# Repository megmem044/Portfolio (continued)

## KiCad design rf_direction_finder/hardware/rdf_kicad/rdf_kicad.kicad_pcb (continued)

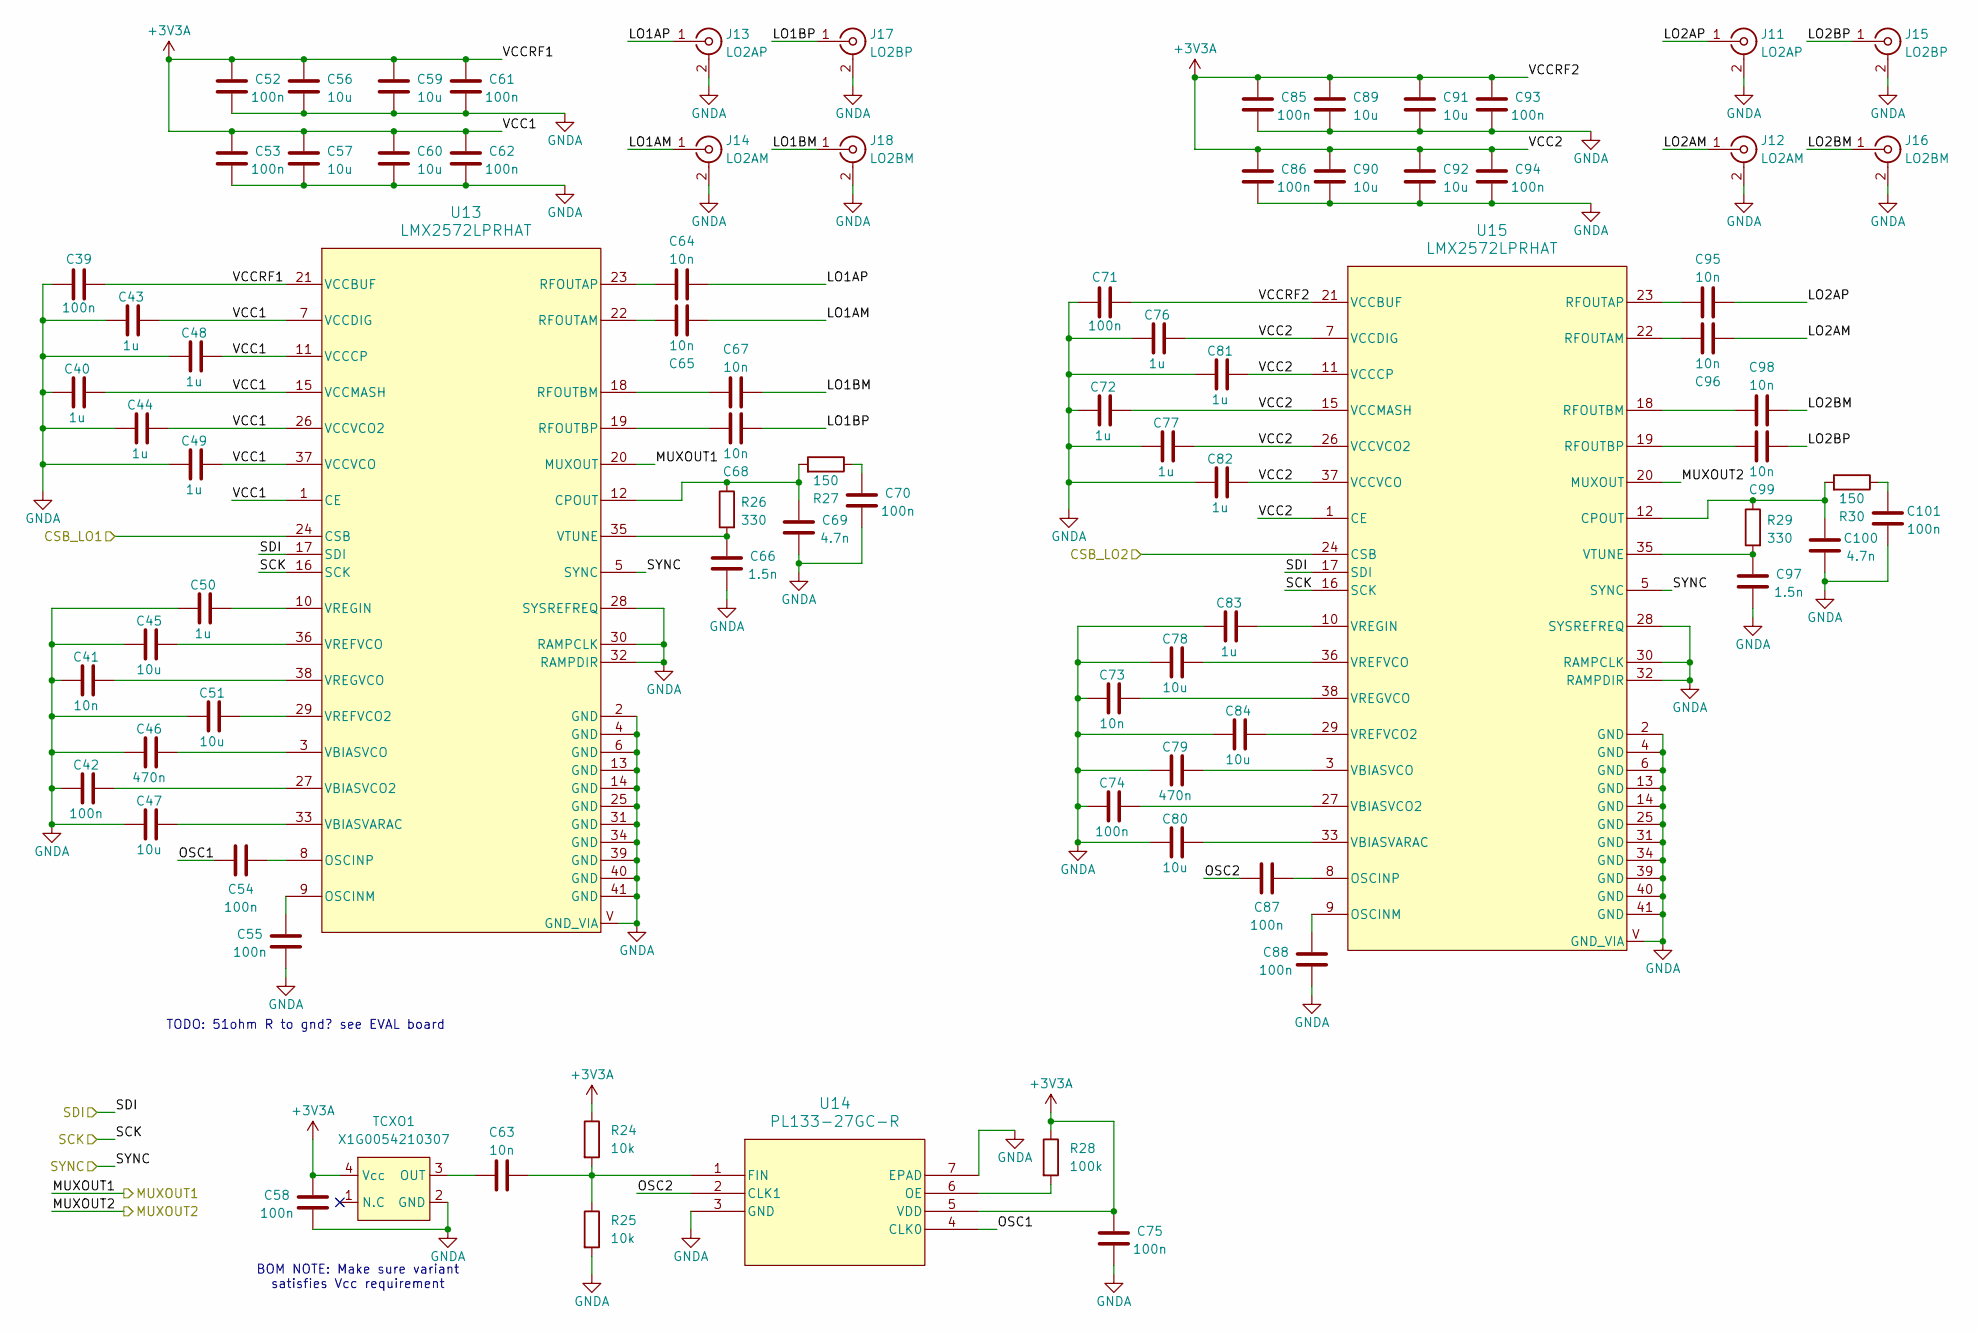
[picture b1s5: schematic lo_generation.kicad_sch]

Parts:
C39, C42, C52, C53, C55, C58, C61, C62, C70, C71, C74, C75, C85, C86, C88, C93, C94, C101: 100n; C_0603_1608Metric_Pad1.08x0.95mm_HandSolder
C40, C43, C44, C48, C49, C50, C72, C76, C77, C81, C82, C83: 1u; C_0603_1608Metric_Pad1.08x0.95mm_HandSolder
C41, C73: 10n; C_0603_1608Metric_Pad1.08x0.95mm_HandSolder
C45, C47, C51, C56, C57, C59, C60, C78, C80, C84, C89, C90, C91, C92: 10u; C_0603_1608Metric_Pad1.08x0.95mm_HandSolder
C46, C79: 470n; C_0603_1608Metric_Pad1.08x0.95mm_HandSolder
C54, C87: 100n; C_0402_1005Metric
C63, C64, C65, C67, C68, C95, C96, C98, C99: 10n; C_0402_1005Metric
C66, C97: 1.5n; C_0603_1608Metric_Pad1.08x0.95mm_HandSolder
C69, C100: 4.7n; C_0603_1608Metric_Pad1.08x0.95mm_HandSolder
J11, J13: LO2AP; U.FL_Molex_MCRF_73412-0110_Vertical
J12, J14: LO2AM; U.FL_Molex_MCRF_73412-0110_Vertical
J15, J17: LO2BP; U.FL_Molex_MCRF_73412-0110_Vertical
J16, J18: LO2BM; U.FL_Molex_MCRF_73412-0110_Vertical
R24, R25: 10k; R_0603_1608Metric_Pad0.98x0.95mm_HandSolder
R26, R29: 330; R_0603_1608Metric_Pad0.98x0.95mm_HandSolder
R27, R30: 150; R_0603_1608Metric_Pad0.98x0.95mm_HandSolder
R28: 100k; R_0603_1608Metric_Pad0.98x0.95mm_HandSolder
TCXO1: X1G0054210307; Crystal_SMD_2520-4Pin_2.5x2.0mm
U13, U15: LMX2572LPRHAT
U14: PL133-27GC-R; PL133_27GC_R

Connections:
+3V3A: C39.1, C40.1, C43.1, C44.1, C48.1, C49.1, C52.2, C53.2, C56.2, C57.2, C58.2, C59.2, C60.2, C61.2, C62.2, C71.1, C72.1, C75.2, C76.1, C77.1, C81.1, C82.1, C85.2, C86.2, C89.2, C90.2, C91.2, C92.2, C93.2, C94.2, R24.1, R28.1, TCXO1.4 (Vcc), U13.1 (CE), U13.7 (VCCDIG), U13.11 (VCCCP), U13.15 (VCCMASH), U13.21 (VCCBUF), U13.26 (VCCVCO2), U13.37 (VCCVCO), U14.5 (VDD), U15.1 (CE), U15.7 (VCCDIG), U15.11 (VCCCP), U15.15 (VCCMASH), U15.21 (VCCBUF), U15.26 (VCCVCO2), U15.37 (VCCVCO); also elsewhere on the board
/RF Frontend/LO Generation/LO1AM: C65.2, J14.1 (In)
/RF Frontend/LO Generation/LO1AP: C64.2, J13.1 (In)
/RF Frontend/LO Generation/LO1BM: C67.2, J18.1 (In)
/RF Frontend/LO Generation/LO1BP: C68.2, J17.1 (In)
/RF Frontend/LO Generation/LO2AM: C96.2, J12.1 (In)
/RF Frontend/LO Generation/LO2AP: C95.2, J11.1 (In)
/RF Frontend/LO Generation/LO2BM: C98.2, J16.1 (In)
/RF Frontend/LO Generation/LO2BP: C99.2, J15.1 (In)
/RF Frontend/LO Generation/OSC1: C54.1, U14.4 (CLK0)
/RF Frontend/LO Generation/OSC2: C87.1, U14.2 (CLK1)
GND: C39.2, C40.2, C41.2, C42.2, C43.2, C44.2, C45.2, C46.2, C47.2, C48.2, C49.2, C50.2, C51.2, C52.1, C53.1, C55.1, C56.1, C57.1, C58.1, C59.1, C60.1, C61.1, C62.1, C66.1, C69.1, C70.1, C71.2, C72.2, C73.2, C74.2, C75.1, C76.2, C77.2, C78.2, C79.2, C80.2, C81.2, C82.2, C83.2, C84.2, C85.1, C86.1, C88.1, C89.1, C90.1, C91.1, C92.1, C93.1, C94.1, C97.1, C100.1, C101.1, J11.2 (Ext), J12.2 (Ext), J13.2 (Ext), J14.2 (Ext), J15.2 (Ext), J16.2 (Ext), J17.2 (Ext), J18.2 (Ext), R25.2, TCXO1.2 (GND), U13.2 (GND), U13.4 (GND), U13.6 (GND), U13.13 (GND), U13.14 (GND), U13.25 (GND), U13.28 (SYSREFREQ), U13.30 (RAMPCLK), U13.31 (GND), U13.32 (RAMPDIR), U13.34 (GND), U13.39 (GND), U13.40 (GND), U13.41 (GND), U13.V (GND_VIA), U14.3 (GND), U14.7 (EPAD), U15.2 (GND), U15.4 (GND), U15.6 (GND), U15.13 (GND), U15.14 (GND), U15.25 (GND), U15.28 (SYSREFREQ), U15.30 (RAMPCLK), U15.31 (GND), U15.32 (RAMPDIR), U15.34 (GND), U15.39 (GND), U15.40 (GND), U15.41 (GND), U15.V (GND_VIA); also elsewhere on the board
unnamed: C70.2, R27.1
unnamed: C101.2, R30.1
unnamed: C63.2, TCXO1.3 (OUT)
unnamed: C69.2, R26.1, R27.2, U13.12 (CPOUT)
unnamed: C55.2, U13.9 (OSCINM)
unnamed: C54.2, U13.8 (OSCINP)
unnamed: C65.1, U13.22 (RFOUTAM)
unnamed: C64.1, U13.23 (RFOUTAP)
unnamed: C67.1, U13.18 (RFOUTBM)
unnamed: C68.1, U13.19 (RFOUTBP)
unnamed: C47.1, U13.33 (VBIASVARAC)
unnamed: C42.1, U13.27 (VBIASVCO2)
unnamed: C46.1, U13.3 (VBIASVCO)
unnamed: C51.1, U13.29 (VREFVCO2)
unnamed: C45.1, U13.36 (VREFVCO)
unnamed: C50.1, U13.10 (VREGIN)
unnamed: C41.1, U13.38 (VREGVCO)
unnamed: C66.2, R26.2, U13.35 (VTUNE)
unnamed: C63.1, R24.2, R25.1, U14.1 (FIN)
unnamed: R28.2, U14.6 (OE)
unnamed: C100.2, R29.1, R30.2, U15.12 (CPOUT)
unnamed: C88.2, U15.9 (OSCINM)
unnamed: C87.2, U15.8 (OSCINP)
unnamed: C96.1, U15.22 (RFOUTAM)
unnamed: C95.1, U15.23 (RFOUTAP)
unnamed: C98.1, U15.18 (RFOUTBM)
unnamed: C99.1, U15.19 (RFOUTBP)
unnamed: C80.1, U15.33 (VBIASVARAC)
unnamed: C74.1, U15.27 (VBIASVCO2)
unnamed: C79.1, U15.3 (VBIASVCO)
unnamed: C84.1, U15.29 (VREFVCO2)
unnamed: C78.1, U15.36 (VREFVCO)
unnamed: C83.1, U15.10 (VREGIN)
unnamed: C73.1, U15.38 (VREGVCO)
unnamed: C97.2, R29.2, U15.35 (VTUNE)
RF_CS_LO1: U13.24 (CSB); also elsewhere on the board
RF_CS_LO2: U15.24 (CSB); also elsewhere on the board
RF_LO_SYNC: U13.5 (SYNC), U15.5 (SYNC); also elsewhere on the board
RF_MOSI: U13.17 (SDI), U15.17 (SDI); also elsewhere on the board
RF_MUXOUT_LO1: U13.20 (MUXOUT); also elsewhere on the board
RF_MUXOUT_LO2: U15.20 (MUXOUT); also elsewhere on the board
RF_SCLK: U13.16 (SCK), U15.16 (SCK); also elsewhere on the board

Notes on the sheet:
TODO: 51ohm R to gnd? see EVAL board
BOM NOTE: Make sure variant satisfies Vcc requirement

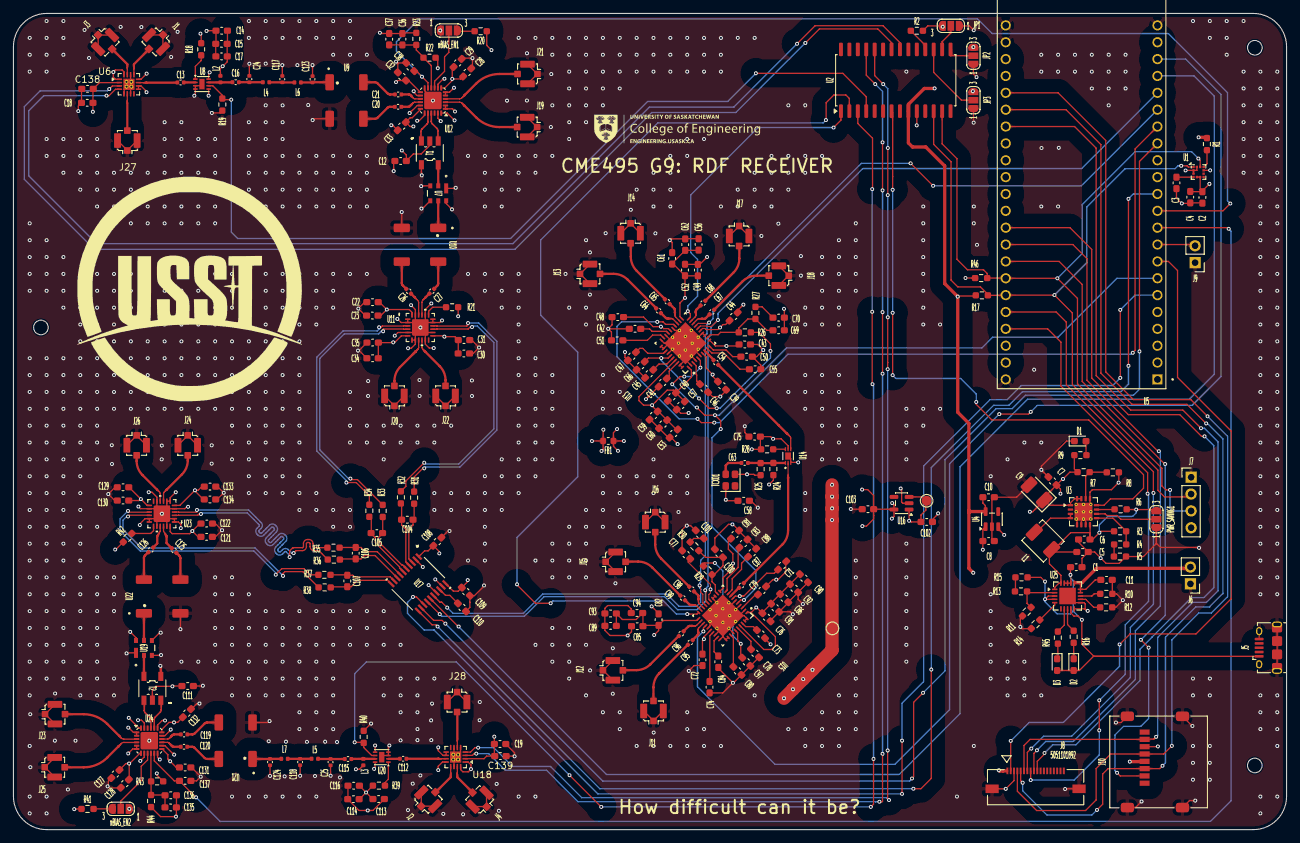
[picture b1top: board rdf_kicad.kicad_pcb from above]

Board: 4 copper layers, 191.8 x 123.0 mm, 258 parts (0 on the bottom side), 184 nets.

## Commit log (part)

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2026-01-31 Initial commit: Toodle To-Do List App
2026-01-31 Move all code into Toodle_ToDo_List_App subfolder
2026-01-31 Add VolunteerHub_VolunteerManagementSystem with core project
2026-02-01 Initial commit: transaction categorization API with SQL aggregation
2026-02-01 Add transaction categorization API project
2026-02-02 Add Java Tic Tac Toe game with tests
2026-02-02 Organize TicTacToe project into its own folder
2026-02-02 Remove compiled output directory from repository
2026-02-02 Add Study Buddy API (FastAPI flashcards backend)
